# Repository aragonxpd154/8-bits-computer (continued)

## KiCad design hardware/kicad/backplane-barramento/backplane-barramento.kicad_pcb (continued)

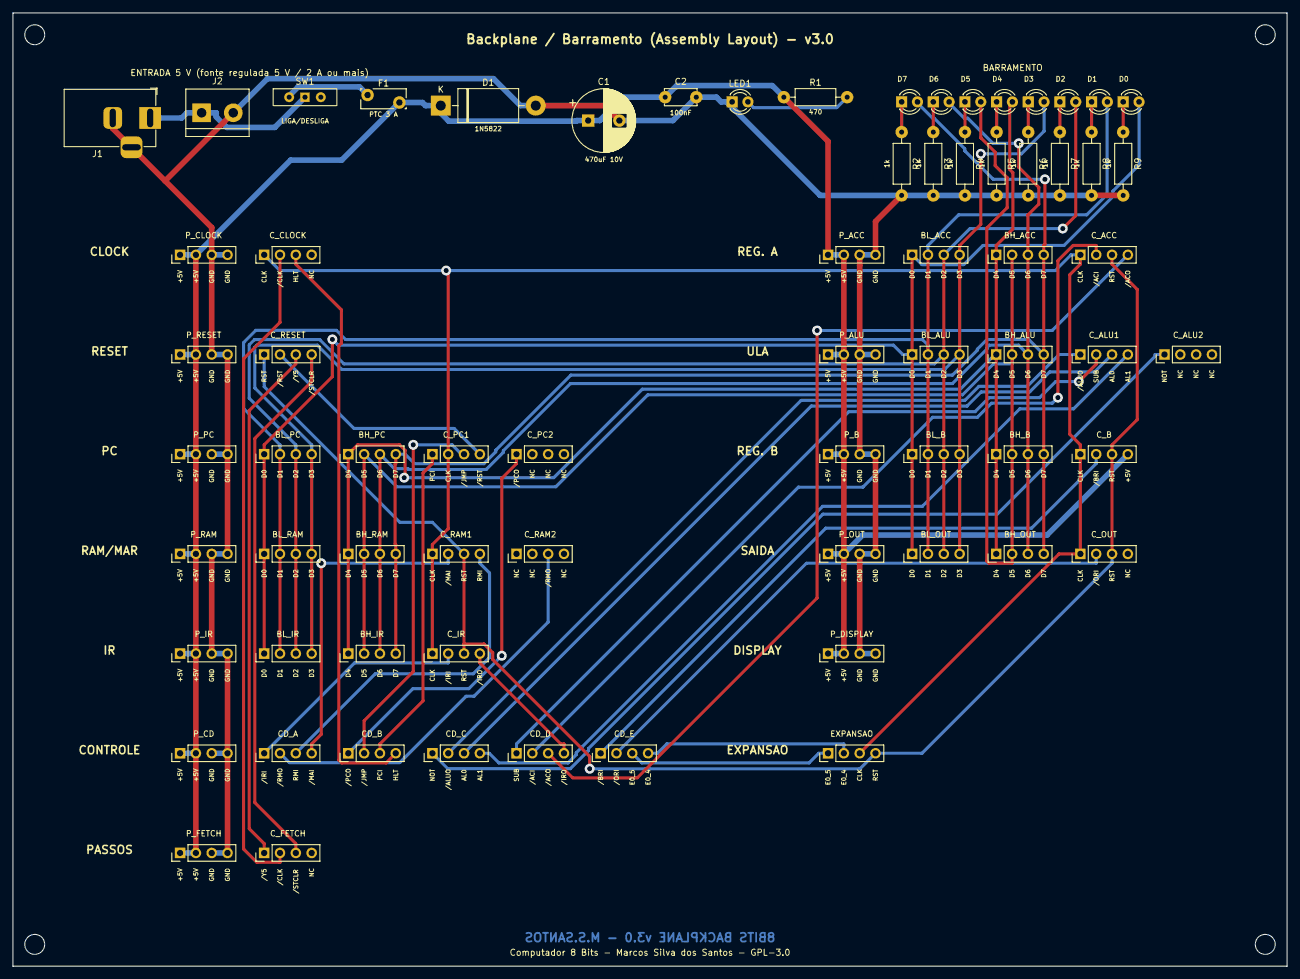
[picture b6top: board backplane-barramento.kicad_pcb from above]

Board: 2 copper layers, 204.5 x 153.0 mm, 74 parts (0 on the bottom side), 47 nets.

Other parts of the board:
H1, H2, H3, H4: MountingHole_3.2mm_M3

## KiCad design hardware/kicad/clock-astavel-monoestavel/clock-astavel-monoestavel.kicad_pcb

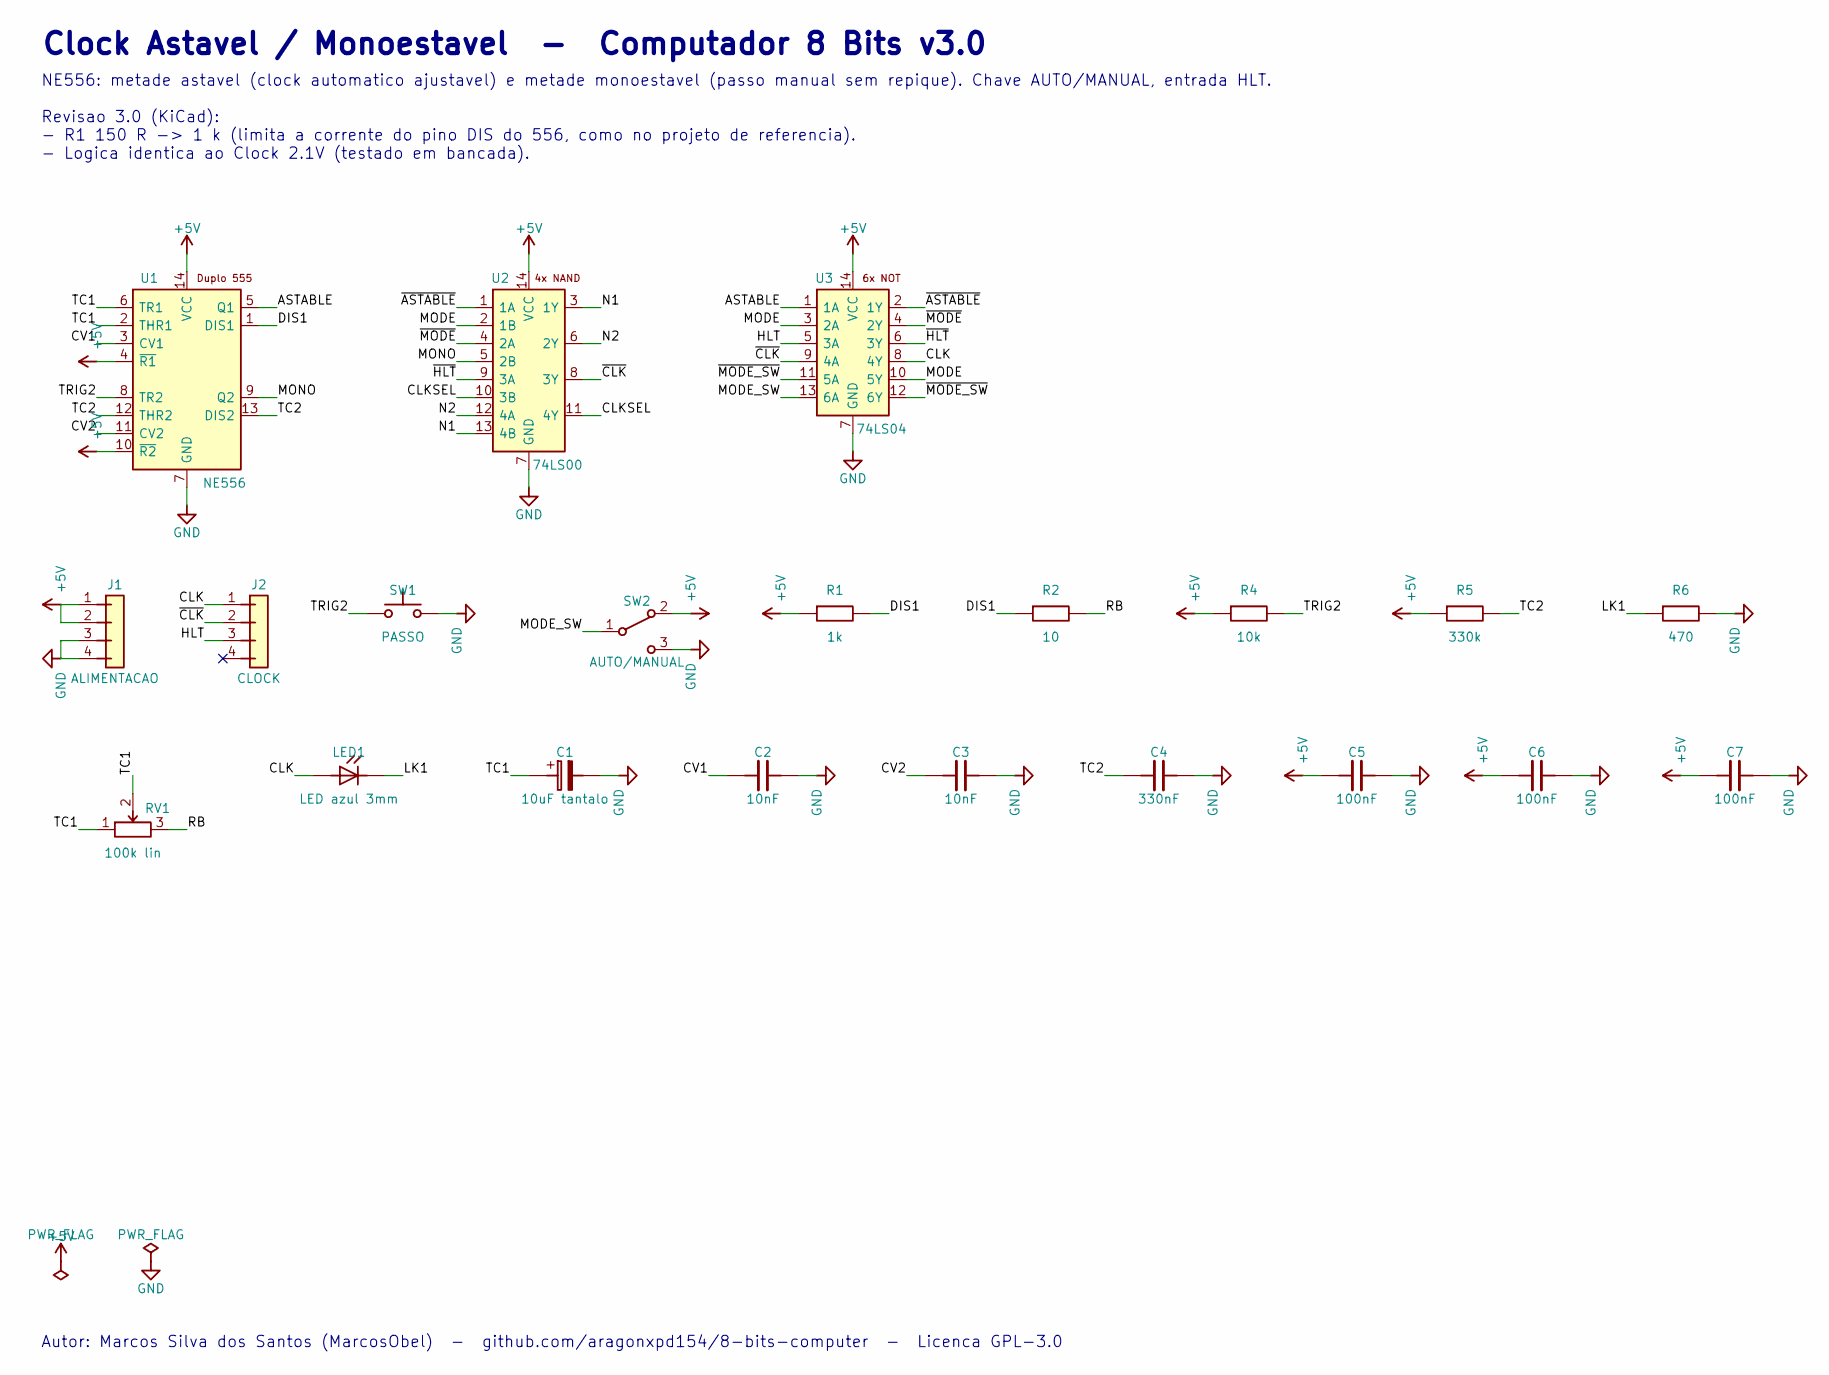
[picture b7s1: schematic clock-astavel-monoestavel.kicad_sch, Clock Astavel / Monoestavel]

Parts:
C1: 10uF tantalo; CP_Radial_Tantal_D4.5mm_P2.50mm
C2, C3: 10nF; C_Disc_D5.0mm_W2.5mm_P5.00mm
C4: 330nF; C_Disc_D5.0mm_W2.5mm_P5.00mm
C5, C6, C7: 100nF; C_Disc_D5.0mm_W2.5mm_P5.00mm
J1: ALIMENTACAO; PinHeader_1x04_P2.54mm_Vertical
J2: CLOCK; PinHeader_1x04_P2.54mm_Vertical
LED1: LED azul 3mm; LED_D3.0mm
R1: 1k; R_Axial_DIN0207_L6.3mm_D2.5mm_P10.16mm_Horizontal
R2: 10; R_Axial_DIN0207_L6.3mm_D2.5mm_P10.16mm_Horizontal
R4: 10k; R_Axial_DIN0207_L6.3mm_D2.5mm_P10.16mm_Horizontal
R5: 330k; R_Axial_DIN0207_L6.3mm_D2.5mm_P10.16mm_Horizontal
R6: 470; R_Axial_DIN0207_L6.3mm_D2.5mm_P10.16mm_Horizontal
RV1: 100k lin; Potentiometer_Alps_RK09K_Single_Vertical
SW1: PASSO; SW_PUSH_6mm
SW2: AUTO/MANUAL; SW_Slide-03_Wuerth-WS-SLTV_10x2.5x6.4_P2.54mm
U1: NE556; DIP-14_W7.62mm_LongPads
U2: 74LS00; DIP-14_W7.62mm_LongPads
U3: 74LS04; DIP-14_W7.62mm_LongPads

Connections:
+5V: C5.1, C6.1, C7.1, J1.1, J1.2, R1.1, R4.1, R5.1, SW2.2 (A), U1.4 (~R1), U1.10 (~R2), U1.14 (VCC), U2.14 (VCC), U3.14 (VCC)
ASTABLE: U1.5 (Q1), U3.1 (1A)
CLK: J2.1, LED1.2 (A), U3.8 (4Y)
CLKSEL: U2.10 (3B), U2.11 (4Y)
CV1: C2.1, U1.3 (CV1)
CV2: C3.1, U1.11 (CV2)
DIS1: R1.2, R2.1, U1.1 (DIS1)
GND: C1.2, C2.2, C3.2, C4.2, C5.2, C6.2, C7.2, J1.3, J1.4, R6.2, SW1.2, SW2.3 (B), U1.7 (GND), U2.7 (GND), U3.7 (GND)
HLT: J2.3, U3.5 (3A)
LK1: LED1.1 (K), R6.1
MODE: U2.2 (1B), U3.3 (2A), U3.10 (5Y)
MODE_SW: SW2.1 (COM), U3.13 (6A)
MONO: U1.9 (Q2), U2.5 (2B)
N1: U2.3 (1Y), U2.13 (4B)
N2: U2.6 (2Y), U2.12 (4A)
RB: R2.2, RV1.3
TC1: C1.1, RV1.1, RV1.2 (W), U1.2 (THR1), U1.6 (TR1)
TC2: C4.1, R5.2, U1.12 (THR2), U1.13 (DIS2)
TRIG2: R4.2, SW1.1, U1.8 (TR2)
~ASTABLE: U2.1 (1A), U3.2 (1Y)
~CLK: J2.2, U2.8 (3Y), U3.9 (4A)
~HLT: U2.9 (3A), U3.6 (3Y)
~MODE_SW: U3.11 (5A), U3.12 (6Y)
~MODE: U2.4 (2A), U3.4 (2Y)

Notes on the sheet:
Clock Astavel / Monoestavel - Computador 8 Bits v3.0
NE556: metade astavel (clock automatico ajustavel) e metade monoestavel (passo manual sem repique). Chave AUTO/MANUAL, entrada HLT. Revisao 3.0 (KiCad): - R1 150 R -> 1 k (limita a corrente do pino DIS do 556, como no projeto de referencia). - Logica identica ao Clock 2.1V (testado em bancada).
Autor: Marcos Silva dos Santos (MarcosObel) - github.com/aragonxpd154/8-bits-computer - Licenca GPL-3.0

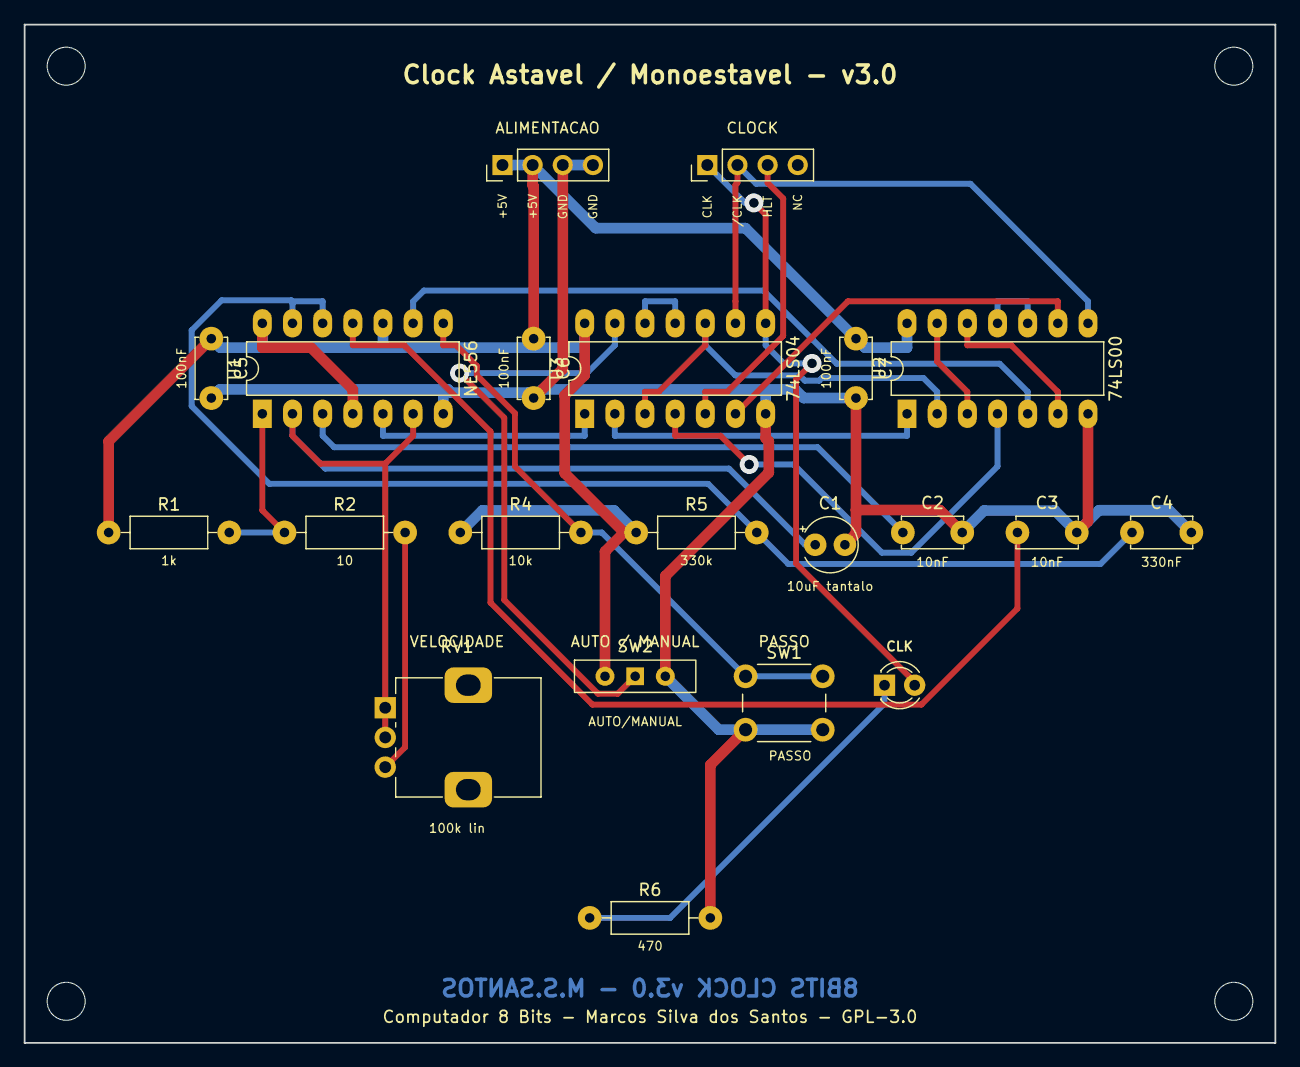
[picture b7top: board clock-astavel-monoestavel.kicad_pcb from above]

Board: 2 copper layers, 105.3 x 85.8 mm, 25 parts (0 on the bottom side), 24 nets.

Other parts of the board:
H1, H2, H3, H4: MountingHole_3.2mm_M3

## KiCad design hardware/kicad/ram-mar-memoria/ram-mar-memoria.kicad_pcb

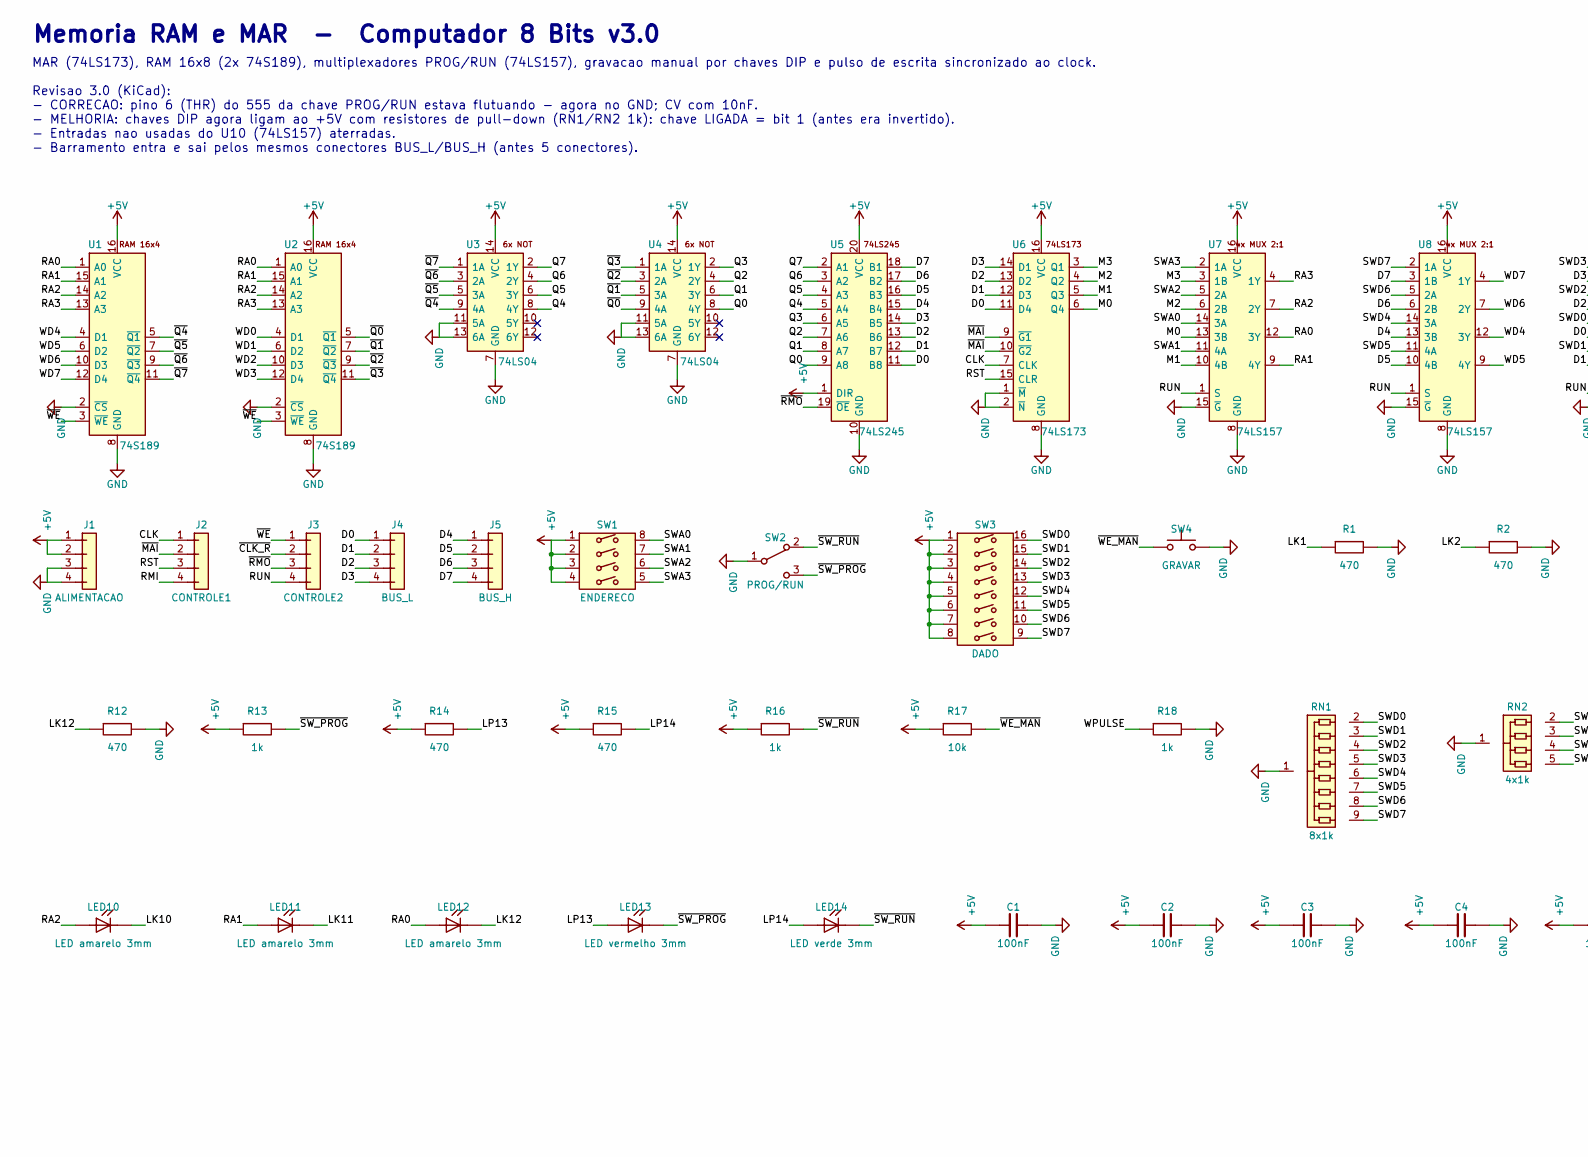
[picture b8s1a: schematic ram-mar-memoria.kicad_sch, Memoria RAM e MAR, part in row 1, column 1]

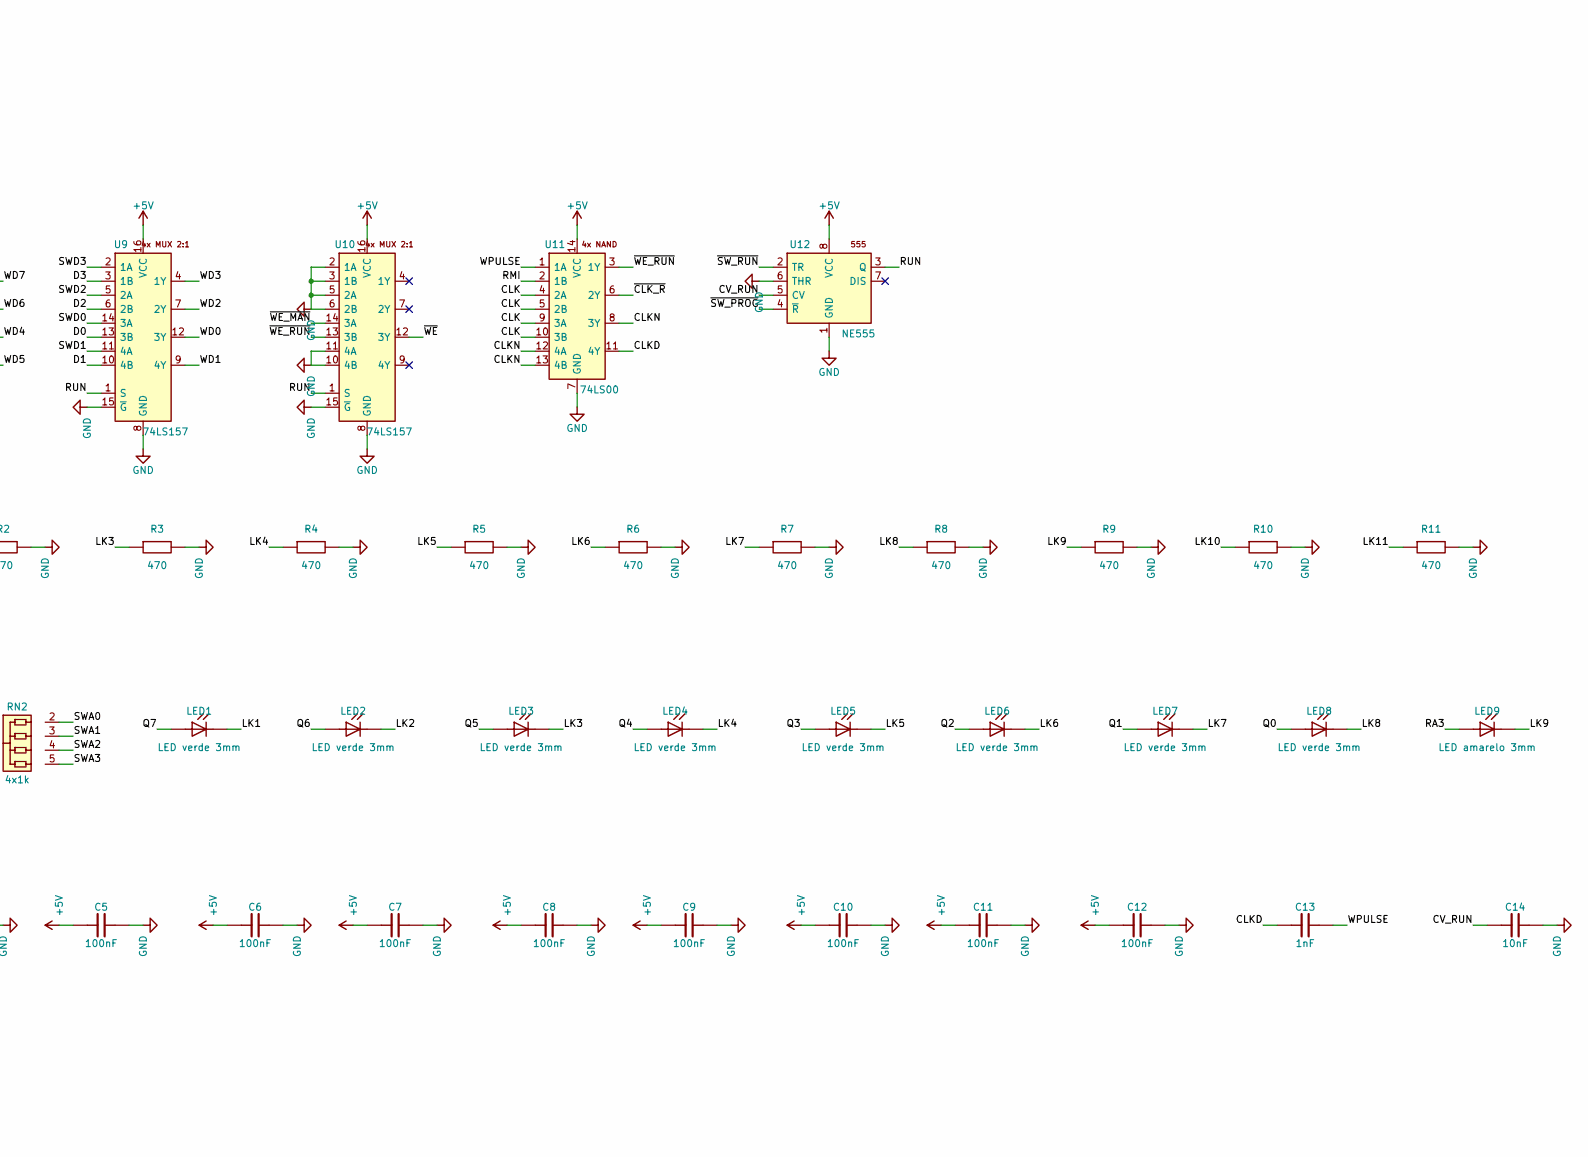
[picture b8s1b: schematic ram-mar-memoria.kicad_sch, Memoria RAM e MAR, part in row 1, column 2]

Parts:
C1, C2, C3, C4, C5, C6, C7, C8, C9, C10, C11, C12: 100nF; C_Disc_D5.0mm_W2.5mm_P5.00mm
C13: 1nF; C_Disc_D5.0mm_W2.5mm_P5.00mm
C14: 10nF; C_Disc_D5.0mm_W2.5mm_P5.00mm
J1: ALIMENTACAO; PinHeader_1x04_P2.54mm_Vertical
J2: CONTROLE1; PinHeader_1x04_P2.54mm_Vertical
J3: CONTROLE2; PinHeader_1x04_P2.54mm_Vertical
J4: BUS_L; PinHeader_1x04_P2.54mm_Vertical
J5: BUS_H; PinHeader_1x04_P2.54mm_Vertical
LED1, LED2, LED3, LED4, LED5, LED6, LED7, LED8, LED14: LED verde 3mm; LED_D3.0mm
LED9, LED10, LED11, LED12: LED amarelo 3mm; LED_D3.0mm
LED13: LED vermelho 3mm; LED_D3.0mm
R1, R2, R3, R4, R5, R6, R7, R8, R9, R10, R11, R12, R14, R15: 470; R_Axial_DIN0207_L6.3mm_D2.5mm_P10.16mm_Horizontal
R13, R16, R18: 1k; R_Axial_DIN0207_L6.3mm_D2.5mm_P10.16mm_Horizontal
R17: 10k; R_Axial_DIN0207_L6.3mm_D2.5mm_P10.16mm_Horizontal
RN1: 8x1k; R_Array_SIP9
RN2: 4x1k; R_Array_SIP5
SW1: ENDERECO; SW_DIP_SPSTx04_Slide_9.78x12.34mm_W7.62mm_P2.54mm
SW2: PROG/RUN; SW_Slide-03_Wuerth-WS-SLTV_10x2.5x6.4_P2.54mm
SW3: DADO; SW_DIP_SPSTx08_Slide_9.78x22.5mm_W7.62mm_P2.54mm
SW4: GRAVAR; SW_PUSH_6mm
U1, U2: 74S189; DIP-16_W7.62mm_LongPads
U3, U4: 74LS04; DIP-14_W7.62mm_LongPads
U5: 74LS245; DIP-20_W7.62mm_LongPads
U6: 74LS173; DIP-16_W7.62mm_LongPads
U7, U8, U9, U10: 74LS157; DIP-16_W7.62mm_LongPads
U11: 74LS00; DIP-14_W7.62mm_LongPads
U12: NE555; DIP-8_W7.62mm_LongPads

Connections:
+5V: C1.1, C2.1, C3.1, C4.1, C5.1, C6.1, C7.1, C8.1, C9.1, C10.1, C11.1, C12.1, J1.1, J1.2, R13.1, R14.1, R15.1, R16.1, R17.1, SW1.1, SW1.2, SW1.3, SW1.4, SW3.1, SW3.2, SW3.3, SW3.4, SW3.5, SW3.6, SW3.7, SW3.8, U1.16 (VCC), U2.16 (VCC), U3.14 (VCC), U4.14 (VCC), U5.1 (DIR), U5.20 (VCC), U6.16 (VCC), U7.16 (VCC), U8.16 (VCC), U9.16 (VCC), U10.16 (VCC), U11.14 (VCC), U12.8 (VCC)
CLK: J2.1, U6.7 (CLK), U11.4 (2A), U11.5 (2B), U11.9 (3A), U11.10 (3B)
CLKD: C13.1, U11.11 (4Y)
CLKN: U11.8 (3Y), U11.12 (4A), U11.13 (4B)
CV_RUN: C14.1, U12.5 (CV)
D0: J4.1, U5.11 (B8), U6.11 (D4), U9.13 (3B)
D1: J4.2, U5.12 (B7), U6.12 (D3), U9.10 (4B)
D2: J4.3, U5.13 (B6), U6.13 (D2), U9.6 (2B)
D3: J4.4, U5.14 (B5), U6.14 (D1), U9.3 (1B)
D4: J5.1, U5.15 (B4), U8.13 (3B)
D5: J5.2, U5.16 (B3), U8.10 (4B)
D6: J5.3, U5.17 (B2), U8.6 (2B)
D7: J5.4, U5.18 (B1), U8.3 (1B)
GND: C1.2, C2.2, C3.2, C4.2, C5.2, C6.2, C7.2, C8.2, C9.2, C10.2, C11.2, C12.2, C14.2, J1.3, J1.4, R1.2, R2.2, R3.2, R4.2, R5.2, R6.2, R7.2, R8.2, R9.2, R10.2, R11.2, R12.2, R18.2, RN1.1 (COM), RN2.1 (COM), SW2.1 (COM), SW4.2, U1.2 (~CS), U1.8 (GND), U2.2 (~CS), U2.8 (GND), U3.7 (GND), U3.11 (5A), U3.13 (6A), U4.7 (GND), U4.11 (5A), U4.13 (6A), U5.10 (GND), U6.1 (~M), U6.2 (~N), U6.8 (GND), U7.8 (GND), U7.15 (~G), U8.8 (GND), U8.15 (~G), U9.8 (GND), U9.15 (~G), U10.2 (1A), U10.3 (1B), U10.5 (2A), U10.6 (2B), U10.8 (GND), U10.10 (4B), U10.11 (4A), U10.15 (~G), U11.7 (GND), U12.1 (GND), U12.6 (THR)
LK1: LED1.1 (K), R1.1
LK2: LED2.1 (K), R2.1
LK3: LED3.1 (K), R3.1
LK4: LED4.1 (K), R4.1
LK5: LED5.1 (K), R5.1
LK6: LED6.1 (K), R6.1
LK7: LED7.1 (K), R7.1
LK8: LED8.1 (K), R8.1
LK9: LED9.1 (K), R9.1
LK10: LED10.1 (K), R10.1
LK11: LED11.1 (K), R11.1
LK12: LED12.1 (K), R12.1
LP13: LED13.2 (A), R14.2
LP14: LED14.2 (A), R15.2
M0: U6.6 (Q4), U7.13 (3B)
M1: U6.5 (Q3), U7.10 (4B)
M2: U6.4 (Q2), U7.6 (2B)
M3: U6.3 (Q1), U7.3 (1B)
Q0: LED8.2 (A), U4.8 (4Y), U5.9 (A8)
Q1: LED7.2 (A), U4.6 (3Y), U5.8 (A7)
Q2: LED6.2 (A), U4.4 (2Y), U5.7 (A6)
Q3: LED5.2 (A), U4.2 (1Y), U5.6 (A5)
Q4: LED4.2 (A), U3.8 (4Y), U5.5 (A4)
Q5: LED3.2 (A), U3.6 (3Y), U5.4 (A3)
Q6: LED2.2 (A), U3.4 (2Y), U5.3 (A2)
Q7: LED1.2 (A), U3.2 (1Y), U5.2 (A1)
RA0: LED12.2 (A), U1.1 (A0), U2.1 (A0), U7.12 (3Y)
RA1: LED11.2 (A), U1.15 (A1), U2.15 (A1), U7.9 (4Y)
RA2: LED10.2 (A), U1.14 (A2), U2.14 (A2), U7.7 (2Y)
RA3: LED9.2 (A), U1.13 (A3), U2.13 (A3), U7.4 (1Y)
RMI: J2.4, U11.2 (1B)
RST: J2.3, U6.15 (CLR)
RUN: J3.4, U7.1 (S), U8.1 (S), U9.1 (S), U10.1 (S), U12.3 (Q)
SWA0: RN2.2 (R1), SW1.8, U7.14 (3A)
SWA1: RN2.3 (R2), SW1.7, U7.11 (4A)
SWA2: RN2.4 (R3), SW1.6, U7.5 (2A)
SWA3: RN2.5 (R4), SW1.5, U7.2 (1A)
SWD0: RN1.2 (R1), SW3.16, U9.14 (3A)
SWD1: RN1.3 (R2), SW3.15, U9.11 (4A)
SWD2: RN1.4 (R3), SW3.14, U9.5 (2A)
SWD3: RN1.5 (R4), SW3.13, U9.2 (1A)
SWD4: RN1.6 (R5), SW3.12, U8.14 (3A)
SWD5: RN1.7 (R6), SW3.11, U8.11 (4A)
SWD6: RN1.8 (R7), SW3.10, U8.5 (2A)
SWD7: RN1.9 (R8), SW3.9, U8.2 (1A)
WD0: U2.4 (D1), U9.12 (3Y)
WD1: U2.6 (D2), U9.9 (4Y)
WD2: U2.10 (D3), U9.7 (2Y)
WD3: U2.12 (D4), U9.4 (1Y)
WD4: U1.4 (D1), U8.12 (3Y)
WD5: U1.6 (D2), U8.9 (4Y)
WD6: U1.10 (D3), U8.7 (2Y)
WD7: U1.12 (D4), U8.4 (1Y)
WPULSE: C13.2, R18.1, U11.1 (1A)
~CLK_R: J3.2, U11.6 (2Y)
~MAI: J2.2, U6.9 (~G1), U6.10 (~G2)
~Q0: U2.5 (~Q1), U4.9 (4A)
~Q1: U2.7 (~Q2), U4.5 (3A)
~Q2: U2.9 (~Q3), U4.3 (2A)
~Q3: U2.11 (~Q4), U4.1 (1A)
~Q4: U1.5 (~Q1), U3.9 (4A)
~Q5: U1.7 (~Q2), U3.5 (3A)
~Q6: U1.9 (~Q3), U3.3 (2A)
~Q7: U1.11 (~Q4), U3.1 (1A)
~RMO: J3.3, U5.19 (~OE)
~SW_PROG: LED13.1 (K), R13.2, SW2.3 (B), U12.4 (~R)
~SW_RUN: LED14.1 (K), R16.2, SW2.2 (A), U12.2 (TR)
~WE_MAN: R17.2, SW4.1, U10.14 (3A)
~WE_RUN: U10.13 (3B), U11.3 (1Y)
~WE: J3.1, U1.3 (~WE), U2.3 (~WE), U10.12 (3Y)

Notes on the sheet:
Memoria RAM e MAR - Computador 8 Bits v3.0
MAR (74LS173), RAM 16x8 (2x 74S189), multiplexadores PROG/RUN (74LS157), gravacao manual por chaves DIP e pulso de escrita sincronizado ao clock. Revisao 3.0 (KiCad): - CORRECAO: pino 6 (THR) do 555 da chave PROG/RUN estava flutuando - agora no GND; CV com 10nF. - MELHORIA: chaves DIP agora ligam a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
Autor: Marcos Silva dos Santos (MarcosObel) - github.com/aragonxpd154/8-bits-computer - Licenca GPL-3.0

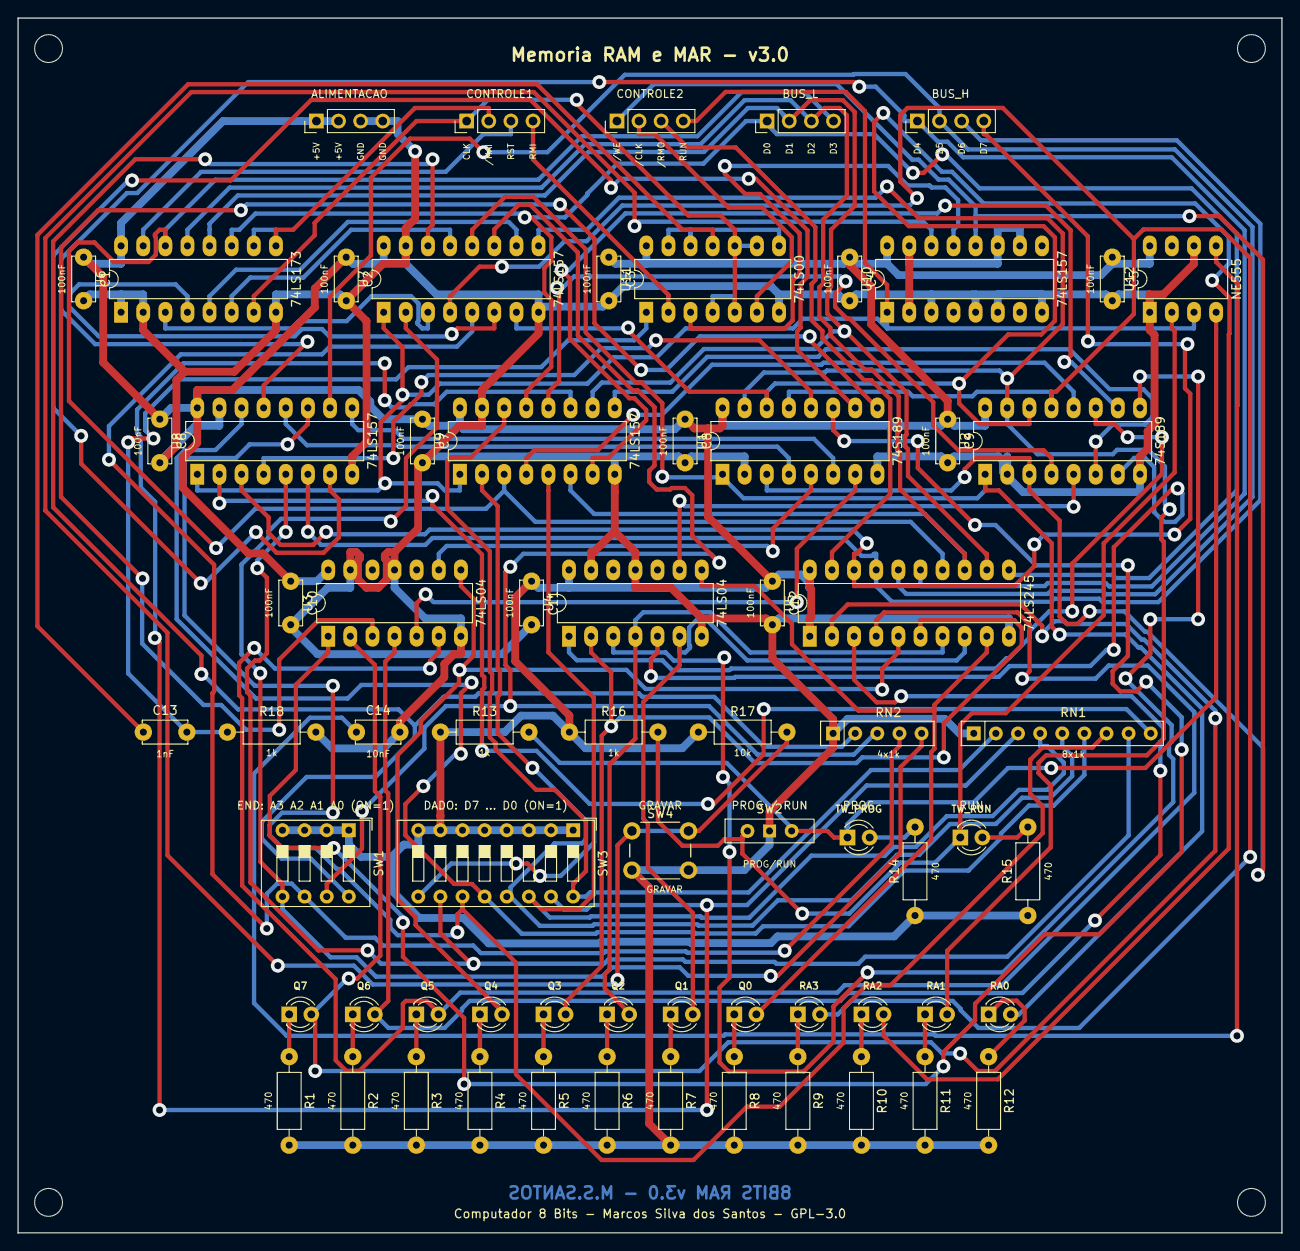
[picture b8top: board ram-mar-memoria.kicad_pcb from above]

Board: 2 copper layers, 145.1 x 139.5 mm, 73 parts (0 on the bottom side), 84 nets.

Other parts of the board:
H1, H2, H3, H4: MountingHole_3.2mm_M3

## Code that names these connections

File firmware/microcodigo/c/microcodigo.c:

/*
 * Gerador do microcodigo - Computador 8 Bits v3.0
 * Autor: Marcos Silva dos Santos (MarcosObel) - GPL-3.0
 *
 * Versao em C para Linux (Zorin OS / Ubuntu) do gerador original de 2021.
 * Compilar:  gcc -O2 -o microcodigo microcodigo.c
 * Executar:  ./microcodigo        (gera EEPROM0.bin, EEPROM1.bin, EEPROM2.bin com 2048 bytes)
 *
 * Endereco: A8=ZF A7=CF A6..A3=opcode A2..A0=passo.
 * Sinais ativos em nivel baixo sao invertidos pela mascara ATIVO_BAIXO_n.
 */
#include <stdio.h>
#include <stdint.h>
#include <string.h>

/* sinal = (eeprom << 8) | mascara */
#define HLT ((2 << 8) | 0x80)
#define PCI ((2 << 8) | 0x40)
#define JMP ((2 << 8) | 0x20)
#define PCO ((2 << 8) | 0x10)
#define MAI ((2 << 8) | 0x08)
#define RMI ((2 << 8) | 0x04)
#define RMO ((2 << 8) | 0x02)
#define IRI ((2 << 8) | 0x01)
#define IRO ((1 << 8) | 0x80)
#define ACO ((1 << 8) | 0x40)
#define ACI ((1 << 8) | 0x20)
#define SUB ((1 << 8) | 0x10)
#define AL1 ((1 << 8) | 0x08)
#define AL0 ((1 << 8) | 0x04)
#define ALU ((1 << 8) | 0x02)
#define NOT ((1 << 8) | 0x01)
#define BRI ((0 << 8) | 0x80)
#define ORI ((0 << 8) | 0x40)

static const uint8_t ATIVO_BAIXO[3] = { 0xC0, 0xE2, 0x3B }; /* EEPROM0, EEPROM1, EEPROM2 */

#define MAXS 6
typedef struct { int n; int s[MAXS]; } passo_t;
#define P(...) { sizeof((int[]){__VA_ARGS__}) / sizeof(int), { __VA_ARGS__ } }
#define VAZIO { 0, { 0 } }

/* passos T2..T4 de cada opcode (T0/T1 = busca, iguais para todos). */
static const passo_t prog[16][3] = {
    /* 0 NOP */ { VAZIO, VAZIO, VAZIO },
    /* 1 LDA */ { P(IRO, MAI), P(RMO, ACI), VAZIO },
    /* 2 LDI */ { P(IRO, ACI), VAZIO, VAZIO },
    /* 3 STA */ { P(IRO, MAI), P(ACO, RMI), VAZIO },
    /* 4 ADD */ { P(IRO, MAI), P(RMO, BRI), P(ALU, ACI) },
    /* 5 SUB */ { P(IRO, MAI), P(RMO, BRI), P(ALU, SUB, ACI) },
    /* 6 AND */ { P(IRO, MAI), P(RMO, BRI), P(ALU, AL0, ACI) },
    /* 7 OR  */ { P(IRO, MAI), P(RMO, BRI), P(ALU, AL1, ACI) },
    /* 8 XOR */ { P(IRO, MAI), P(RMO, BRI), P(ALU, AL1, AL0, ACI) },
    /* 9 NOT */ { P(ALU, AL1, AL0, NOT, ACI), VAZIO, VAZIO },
    /* A JMP */ { P(IRO, JMP), VAZIO, VAZIO },
    /* B JC  */ { VAZIO, VAZIO, VAZIO },   /* tratado abaixo (depende de CF) */
    /* C JZ  */ { VAZIO, VAZIO, VAZIO },   /* tratado abaixo (depende de ZF) */
    /* D --  */ { VAZIO, VAZIO, VAZIO },
    /* E OUT */ { P(ACO, ORI), VAZIO, VAZIO },
    /* F HLT */ { P(HLT), VAZIO, VAZIO },
};
static const passo_t busca[2] = { P(PCO, MAI), P(RMO, IRI, PCI) };
static const passo_t salto = P(IRO, JMP);

static uint8_t rom[3][2048];

static void aplica(int addr, const passo_t *p)
{
    for (int i = 0; i < p->n; i++)
        rom[p->s[i] >> 8][addr] |= (uint8_t)(p->s[i] & 0xFF);
}

int main(void)
{
    memset(rom, 0, sizeof rom);
    for (int addr = 0; addr < 2048; addr++) {
        int passo = addr & 7, op = (addr >> 3) & 15, cf = (addr >> 7) & 1, zf = (addr >> 8) & 1;
        if (passo < 2)
            aplica(addr, &busca[passo]);
        else if (passo < 5) {
            if (op == 0xB) { if (cf && passo == 2) aplica(addr, &salto); }
            else if (op == 0xC) { if (zf && passo == 2) aplica(addr, &salto); }
            else aplica(addr, &prog[op][passo - 2]);
        }
        for (int e = 0; e < 3; e++)
            rom[e][addr] ^= ATIVO_BAIXO[e];
    }
    for (int e = 0; e < 3; e++) {
        char nome[32];
        snprintf(nome, sizeof nome, "EEPROM%d.bin", e);
        FILE *f = fopen(nome, "wb");
        if (!f) { perror(nome); return 1; }
        fwrite(rom[e], 1, sizeof rom[e], f);
        fclose(f);
    }
    printf("Arquivos binarios gerados com sucesso! (EEPROM2 -> U1, EEPROM1 -> U2, EEPROM0 -> U3)\n");
    return 0;
}

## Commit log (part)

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2021-10-02 Accumulators and Registrars 1.0V
2021-10-03 Description
2021-10-03 1.0V
2021-10-03 Electronic Schem and List BOM
2021-10-03 UPDATE DESCRIPTION
2021-10-04 UPDATE
    Atualização das rotas e linhas de cobre.
2021-10-05 PCB UPLOAD
2021-10-05 UPDATE CIRCUIT
2021-10-05 UPDATE FIX
2021-10-07 REHEARSAL
2021-10-07 SOURCE
2021-10-07 SCHEME
2021-10-08 INSTANCIA
2021-10-13 UPDATE PCB
2021-10-13 UPDATE FIX DESCRIPTION
2021-10-17 UPDATE FIX TO PCB
2021-10-19 TEST IN PCB
2021-10-20 UPDATE INFO
2021-10-20 UPLOAD TO 3DVIEWER
2021-10-21 RESERT CIRCUIT
2021-10-21 VIDEO TEST DEVELOPER
2021-10-21 INTRUCTION REGISTER
2021-10-27 UP INFO
2021-10-28 Assembly Layout
2021-10-28 PROGRAM COUNTER PROJECTS
2021-10-28 PCB 1.0V
2021-10-28 2.0V
2021-10-28 3.0V
2021-10-28 UPDATE FIX PCB
2021-10-28 UPDATE BY INFO
2021-10-31 OUTPUT REGISTER
2021-12-04 UP FIX
2023-01-04 Revisão dos arquivos datados de 2021/2022
2023-01-04 Revisão esquemas datados de 2021/2022
2023-01-05 Preparando para revisão total do projet
    Será feita toda a preparação para revisão, provendo a conclusão do
    projeto e esquema eletronico PCB ate o final desse ano de 2023
2023-01-05 Preparando para revisão total do projeto
    Será feita toda a preparação para revisão, provendo a conclusão do
    projeto e esquema eletronico PCB ate o final desse ano de 2023.
2023-01-05 ~ ~ ~ ~ ~ ~ ~ ~ ~ ~ ~ ~ ~ ~ ~ ~ ~ ~ ~ ~ ~ ~ ~ ~ ~ ~ ~ ~ ~ ~ ~ ~ ~ ~ ~ ~ ~ .git/COMMIT_EDITMSG [unix] (17:49 05/01/2023) 1,1 All -- INSERT --
    ~
    ~
    ~
    ~
    ~
    ~
2023-01-14 Preparando para documentação
2023-01-14 Inserindo informações de REAME do repositório
2023-01-14 Inserindo tags para documentação
2023-01-14 Adicionando algumas informações documentadas
2023-01-14 Corrigindo aquivos documentados
2023-01-14 Inserindo status e documentação do projeto
2023-01-14 Acertando status de desenvolvimento
2023-01-14 Desfazendo alterações
2023-01-29 Atualizando documentação
